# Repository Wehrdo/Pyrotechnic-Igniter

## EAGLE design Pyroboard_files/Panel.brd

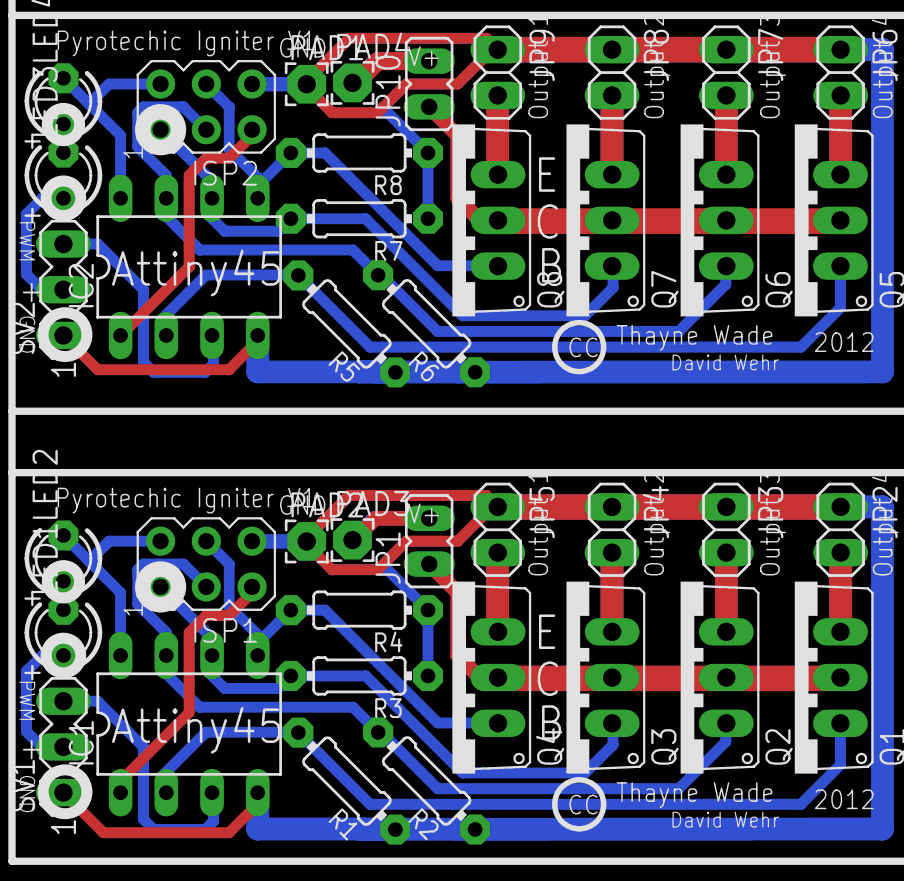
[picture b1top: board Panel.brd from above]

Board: 2 copper layers, 40 parts (0 on the bottom side), 32 nets.

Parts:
IC1, IC2: TINY85; DIL08
ISP1, ISP2: AVRISP-6; AVRISP
JP1, JP10: JP1
JP2, JP3, JP4, JP5, JP6, JP7, JP8, JP9: 1X02
LED1, LED2, LED3, LED4: LED3MM
PAD1, PAD2: - Flight Pack; 2,15/1,0
PAD3, PAD4: + Flight Pack; 2,15/1,0
Q1, Q2, Q3, Q4, Q5, Q6, Q7, Q8: TO220V
R1, R2, R3, R4, R5, R6, R7, R8: 1M; 0204/7
SV1, SV2: MA03-1

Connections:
+5V: IC1.8, ISP1.2, LED2.K
+5V1: IC2.8, ISP2.2, LED4.K
FP: JP1.1, Q1.2, Q2.2, Q3.2, Q4.2
FP1: JP10.1, Q5.2, Q6.2, Q7.2, Q8.2
GND: IC1.4, ISP1.6, JP2.1, JP3.1, JP4.1, JP5.1, PAD2.1, R1.1, R2.1, R3.1, R4.1, SV1.1
GND1: IC2.4, ISP2.6, JP6.1, JP7.1, JP8.1, JP9.1, PAD1.1, R5.1, R6.1, R7.1, R8.1, SV2.1
unnamed: IC1.7, ISP1.3, Q2.1, R2.2
unnamed: IC1.6, ISP1.1, Q3.1, R3.2
unnamed: JP1.2, PAD3.1
unnamed: IC1.1, ISP1.5
unnamed: IC1.3, SV1.3
unnamed: LED1.A, SV1.2
unnamed: LED1.K, LED2.A
unnamed: IC1.2, Q1.1, R1.2
unnamed: JP2.2, Q1.3
unnamed: JP3.2, Q2.3
unnamed: JP4.2, Q3.3
unnamed: JP5.2, Q4.3
unnamed: IC2.7, ISP2.3, Q6.1, R6.2
unnamed: IC2.6, ISP2.1, Q7.1, R7.2
unnamed: IC1.5, ISP1.4, Q4.1, R4.2
unnamed: IC2.1, ISP2.5
unnamed: IC2.3, SV2.3
unnamed: IC2.2, Q5.1, R5.2
unnamed: JP6.2, Q5.3
unnamed: JP7.2, Q6.3
unnamed: JP8.2, Q7.3
unnamed: JP9.2, Q8.3
unnamed: LED3.A, SV2.2
unnamed: LED3.K, LED4.A
unnamed: IC2.5, ISP2.4, Q8.1, R8.2
unnamed: JP10.2, PAD4.1

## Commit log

2012-07-08 Added main code
2012-07-08 Adjust threshold values to more likely work with all transmitters.
2012-07-15 new file: pyrotechnic_igniter/4 output Igniter.brd new file: pyrotechnic_igniter/4 output Igniter.sch new file: pyrotechnic_igniter/Panel.brd
2012-07-15 Attiny 45/85 Board File (Cadsoft Eagle) Attiny 45/85 Board Schematic (Cadsoft Eagle) Attiny 45/85 Board Pannel 5cm x 5cm
2012-07-15 deleted: pyrotechnic_igniter/4 output Igniter.brd deleted: pyrotechnic_igniter/4 output Igniter.sch deleted: pyrotechnic_igniter/Panel.brd
2012-09-08 Minor compatibility mod
    Threshold info, output pins (Specific to Attiny 45/85 board)
2012-09-10 Added pdf for toner transfer.
2014-04-02 Typo
    Accidentally wrote 3 ms instead of 3000 ms.
